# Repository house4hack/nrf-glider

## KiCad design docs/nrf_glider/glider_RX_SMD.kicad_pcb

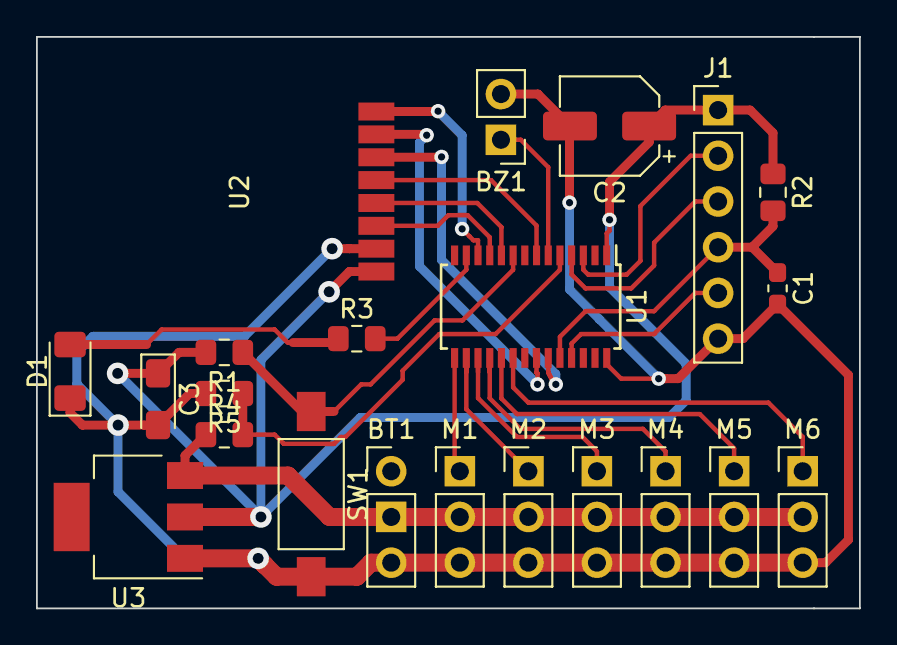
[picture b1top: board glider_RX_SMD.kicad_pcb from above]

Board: 2 copper layers, 45.7 x 31.8 mm, 22 parts (0 on the bottom side), 24 nets.

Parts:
BT1: 4.5V - 7.2V; PinHeader_1x03_P2.54mm_Vertical
BZ1: Buzzer; PinHeader_1x02_P2.54mm_Vertical
C1: 10n; C_0603_1608Metric_Pad1.05x0.95mm_HandSolder
C2: 10uF; CP_Elec_5x5.8
C3: 22uF Tan; CP_EIA-3216-18_Kemet-A_Pad1.58x1.35mm_HandSolder
D1: LED; LED_1206_3216Metric_Pad1.42x1.75mm_HandSolder
J1: PROG; PinHeader_1x06_P2.54mm_Vertical
M1, M3, M4, M5, M6: Servo Left; PinHeader_1x03_P2.54mm_Vertical
M2: Servo Right; PinHeader_1x03_P2.54mm_Vertical
R1: 4k7; R_0805_2012Metric_Pad1.15x1.40mm_HandSolder
R2: 47k; R_0805_2012Metric_Pad1.15x1.40mm_HandSolder
R3: 220; R_0805_2012Metric_Pad1.15x1.40mm_HandSolder
R4: 20k; R_0805_2012Metric_Pad1.15x1.40mm_HandSolder
R5: 10k; R_0805_2012Metric_Pad1.15x1.40mm_HandSolder
SW1: Pair; SW_SPST_FSMSM
U1: MSP430G2553IPW28; TSSOP-28_4.4x9.7mm_P0.65mm
U2: NRF24L01_Breakout; NRF24L01-SMD
U3: LM1117-3.3; SOT-223

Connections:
GND: BT1.2, BZ1.2, C1.2, C2.2, C3.2, D1.1, J1.6, M1.3, M2.3, M3.3, M4.3, M5.3, M6.3, R5.2, SW1.2, U1.28, U2.1, U3.1
unnamed: BZ1.1, U1.6
unnamed: C1.1, J1.4, R2.2, U1.24
unnamed: D1.2, R3.1
unnamed: J1.2, U1.3
unnamed: J1.3, U1.4
unnamed: J1.5, U1.25
unnamed: M1.1, U1.15
unnamed: M2.1, U1.16
unnamed: M3.1, U1.17
unnamed: M4.1, U1.18
unnamed: M5.1, U1.19
unnamed: M6.1, U1.20
unnamed: R1.1, SW1.1, U1.9
unnamed: R3.2, U1.13
unnamed: R4.2, R5.1, U1.5
unnamed: U1.7, U2.5
unnamed: U1.10, U2.4
unnamed: U1.11, U2.3
unnamed: U1.12, U2.8
unnamed: U1.22, U2.7
unnamed: U1.23, U2.6
VCC: C2.1, C3.1, J1.1, R1.2, R2.1, U1.1, U2.2, U3.2
VDD: BT1.1, M1.2, M2.2, M3.2, M4.2, M5.2, M6.2, R4.1, U3.3

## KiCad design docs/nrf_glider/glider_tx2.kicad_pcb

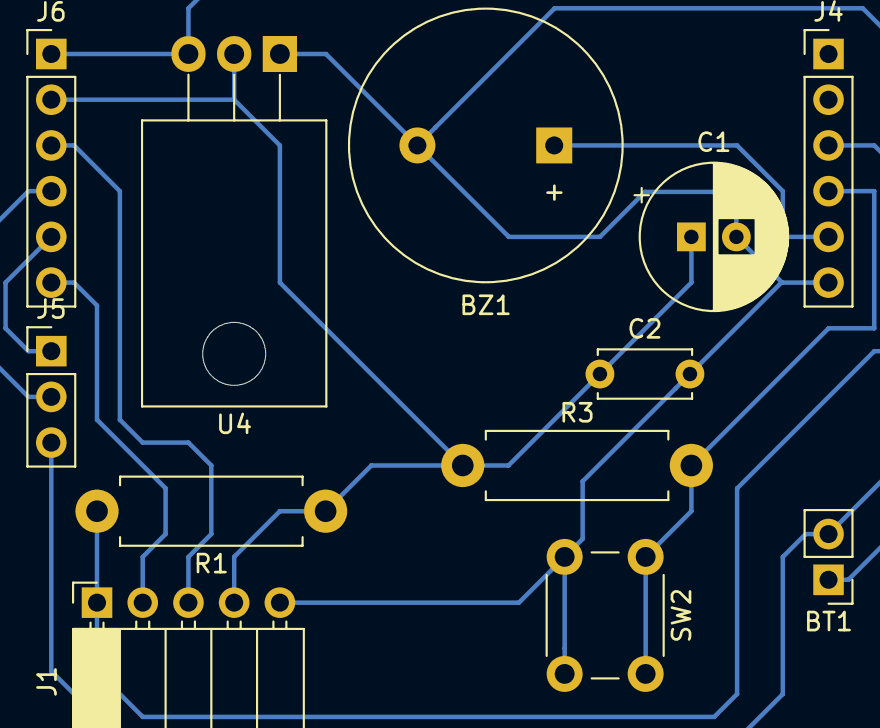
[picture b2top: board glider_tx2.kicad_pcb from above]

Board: 2 copper layers, 12 parts (0 on the bottom side), 10 nets.

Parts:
BT1: 4.5V - 9.9V; PinHeader_1x02_P2.54mm_Vertical
BZ1: Buzzer; Buzzer_15x7.5RM7.6
C1: 10uF; CP_Radial_D8.0mm_P2.50mm
C2: 100nF; C_Disc_D5.0mm_W2.5mm_P5.00mm
J1: Conn_01x05_Female; PinSocket_1x05_P2.54mm_Horizontal
J4, J6: Conn_01x06_Female; PinHeader_1x06_P2.54mm_Vertical
J5: UART; PinHeader_1x03_P2.54mm_Vertical
R1, R3: 4k7; R_Axial_DIN0411_L9.9mm_D3.6mm_P12.70mm_Horizontal
SW2: TRIM; SW_PUSH_6mm_H5mm
U4: LM1117-3.3; TO-220-3_Horizontal_TabDown

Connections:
GND: BT1.2, BZ1.2, C1.2, C2.2, J1.5, J4.6, J5.3, SW2.2, U4.1
unnamed: BZ1.1, J4.5
unnamed: J1.1, J4.3, R1.2
unnamed: J1.2, J6.6
unnamed: J1.3, J6.3
unnamed: J4.4, R3.2, SW2.1
unnamed: J5.1, J6.5
unnamed: J5.2, J6.4
VCC: C1.1, C2.1, J1.4, J6.2, R1.1, R3.1, U4.2
VDD: BT1.1, J6.1, U4.3

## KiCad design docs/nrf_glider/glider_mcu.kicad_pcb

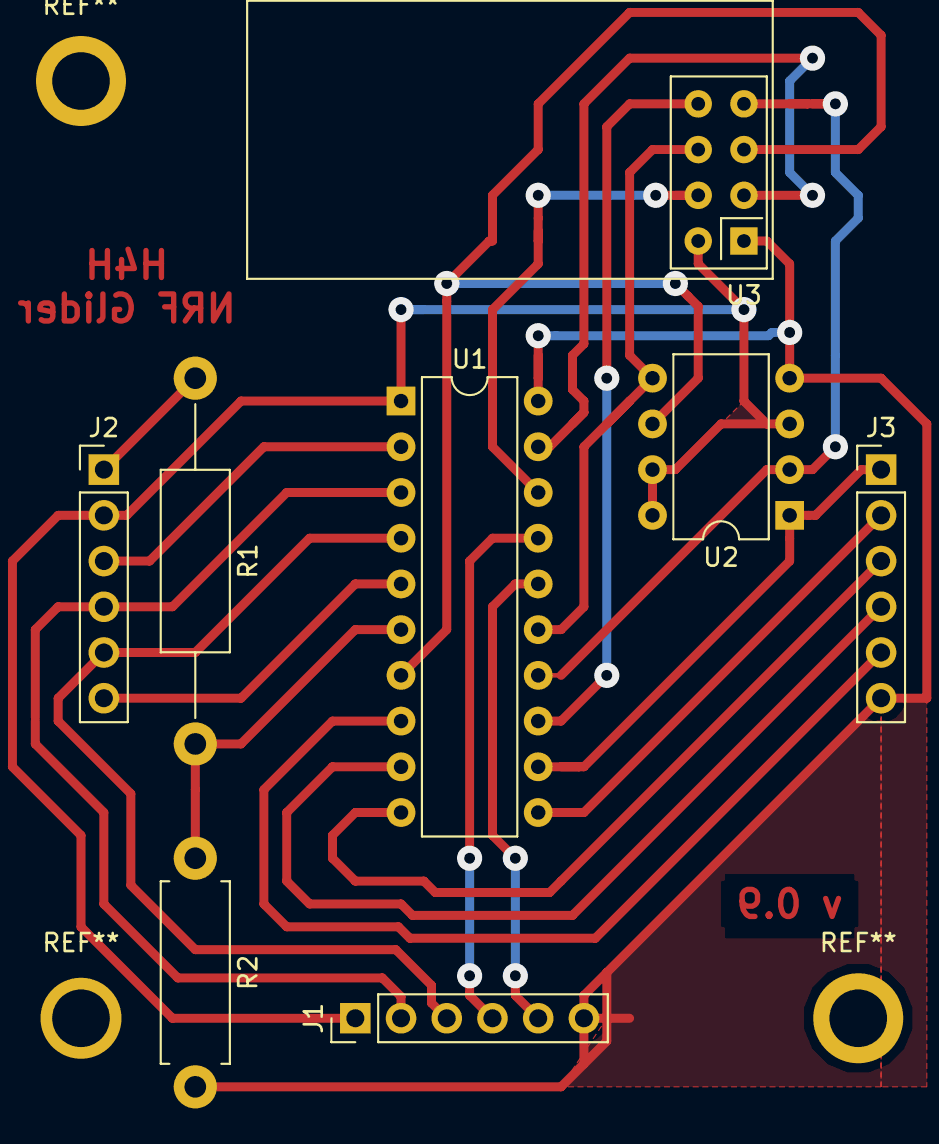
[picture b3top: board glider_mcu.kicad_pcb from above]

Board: 2 copper layers, 8 parts (0 on the bottom side), 21 nets.

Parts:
J1: PROG; PinHeader_1x06_P2.54mm_Vertical
J2, J3: Conn_01x06_Male; PinHeader_1x06_P2.54mm_Vertical
R1: 20k; R_Axial_DIN0411_L9.9mm_D3.6mm_P20.32mm_Horizontal
R2: 10k; R_Axial_DIN0411_L9.9mm_D3.6mm_P12.70mm_Horizontal
U1: MSP430G2553IPW20; DIP-20_W7.62mm
U2: 25LC640; DIP-8_W7.62mm
U3: NRF24L01_Breakout; nRF24L01_Breakout

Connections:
GND: J1.6, J3.6, R2.2, U1.20, U2.4, U3.1
unnamed: J1.2, J2.4, U1.3
unnamed: J1.3, J2.5, U1.4
unnamed: J1.4, U1.17
unnamed: J1.5, U1.16
unnamed: J2.3, U1.2
unnamed: J2.6, U1.5
unnamed: J3.1, U1.12, U2.1
unnamed: J3.2, U1.11
unnamed: J3.3, U1.10
unnamed: J3.4, U1.9
unnamed: J3.5, U1.8
unnamed: R1.2, R2.1, U1.6
unnamed: U1.7, U2.6, U3.5
unnamed: U1.13, U3.8
unnamed: U1.14, U2.2, U3.7
unnamed: U1.15, U2.5, U3.6
unnamed: U1.18, U3.4
unnamed: U1.19, U3.3
VCC: J1.1, J2.2, U1.1, U2.3, U2.7, U2.8, U3.2
VDD: J2.1, R1.1

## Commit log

2016-09-17 cleanup
2016-09-17 Testing various parameters
2016-09-17 2mbps version
2016-09-20 dropped to 250kbps
2016-09-20 added battery test and actual controls, switched up to 1mbps with ack
2016-09-20 250kbps, small payload for max range
2016-09-21 rx: return to middle if no signal, put limits on movement, battery and no signal warnings
2016-09-21 added mixing of tx, also end stop limits and mix factor
2016-09-25 added trim control on tamatieberg
2018-05-22 converted to PlatformIO for VSCode
2018-05-22 fix data rate, should be 250kbps
2018-07-03 move libs to libs folder
2018-07-03 moved libs to libs folder
2018-09-20 change frequency to 250kbps, remove annoying buzzer, gentle return-to-zero
2018-09-21 trim control
2018-09-21 avoid extreme trims
2018-09-21 solution for noise during debugging
2018-09-21 beep if no radio for over 2 seconds, for finding after landing
2018-10-09 added sensitivity control
2018-10-09 rough schematics
2018-10-23 kicad schematic first draft
2018-10-23 add CS for eeprom, add UART connector on TX module
2018-10-23 tweaks to schematic
2018-10-23 added switch
2018-10-24 Added some footprints
2018-10-24 split up schematic into 3
2018-10-24 added hierarchical sheets and labels
2018-10-24 remove and ignore bak files
2018-10-24 ignore netlist files
2018-11-02 glider plans
2018-11-06 fixed /WP pin on EEPROM
2018-11-06 fix nrf SPI connection
2018-11-06 Modified pinout to connectors
2018-11-06 Version 1 routing
2018-11-06 Version 2 routing
2018-11-11 Version 2 routing PDF
2018-11-14 Rerouted Rx module for center buzzer
2018-11-14 Added a TX2 which only has a header for the joystick and no switch on psu
2018-12-04 added saving data to flash
2018-12-04 remove test code, allow bigger trims
2018-12-04 refactoring, menu to set channel and sensitivity
2018-12-04 added version flag for v1 hardware
2018-12-04 fix nrf pins
2018-12-04 update hardware v2
2018-12-04 fix compile error
2018-12-04 added flash lib to rx
2018-12-11 extract config into header
2018-12-11 use the new header
2018-12-11 multiple environments for the different versions
2018-12-17 Updates from Witsieshoek
2018-12-18 debug display of actual joystick values
2019-01-05 add version to menu
2019-01-08 refactoring wip
2019-01-08 pass pointers rather
2019-01-08 update flags
2019-01-08 parsing of command input working
2019-01-08 working gcode-style interaction
2019-01-08 refactor nrf pins
2019-01-08 restart radio if channel changes
2019-01-08 Added a SMD version of the RX board
2019-01-22 wip - invert and swap axes
2019-01-22 settings for axes inversion/swap
2019-01-22 mix factor, exponential wip
2019-01-22 added verbose mode to allowchecking inputs
2019-01-22 added joystick calibration and an exponential approximation
2019-01-22 best exponential implementation
2019-01-22 reduce max exponential to 2
2019-01-24 added wifi and webpage code from fishfeeder
2019-01-24 use TX1 for debug output, TX0 will talk to MSP
2019-01-26 sending of commands
2019-01-26 pasting many commands - wip
2019-01-26 buffered serial handling
2019-01-26 remove delay which was causing serial dropout
2019-01-26 tweaks
2019-05-28 increase RX sensitivity
